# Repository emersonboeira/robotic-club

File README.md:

# robotic-club
Our robotics club repository

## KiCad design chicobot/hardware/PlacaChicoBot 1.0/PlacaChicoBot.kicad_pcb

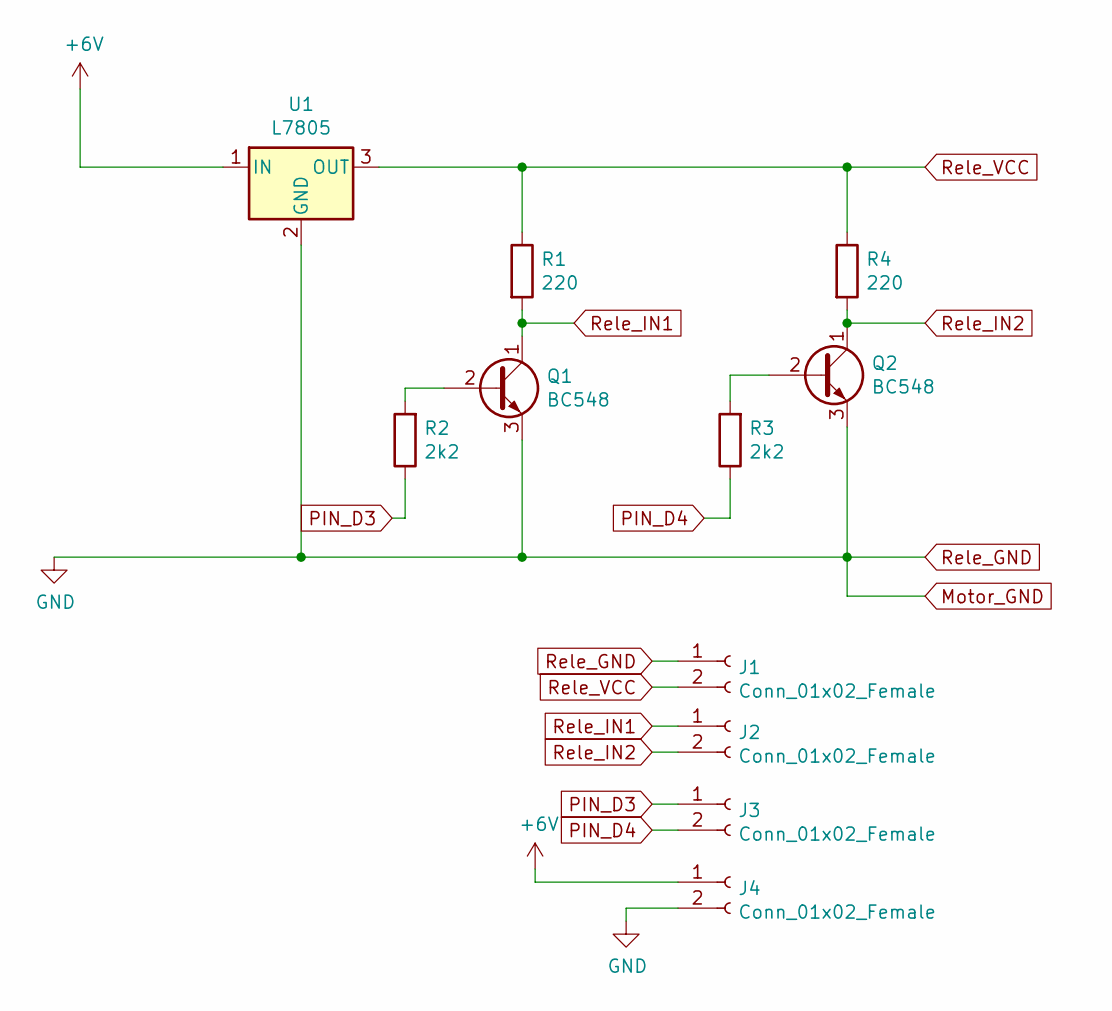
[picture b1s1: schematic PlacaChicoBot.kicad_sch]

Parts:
J1, J2, J3, J4: Conn_01x02_Female; TerminalBlock_Phoenix_MPT-0,5-2-2.54_1x02_P2.54mm_Horizontal
Q1, Q2: BC548; TO-92_Inline
R1, R4: 220; R_Axial_DIN0309_L9.0mm_D3.2mm_P12.70mm_Horizontal
R2, R3: 2k2; R_Axial_DIN0309_L9.0mm_D3.2mm_P12.70mm_Horizontal
U1: L7805; TO-220-3_Vertical

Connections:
+6V: J4.1, U1.1 (IN)
Motor_GND: J1.1, J4.2, Q1.3 (E), Q2.3 (E), U1.2 (GND)
unnamed: Q1.2 (B), R2.2
unnamed: Q2.2 (B), R3.2
PIN_D3: J3.1, R2.1
PIN_D4: J3.2, R3.1
Rele_IN1: J2.1, Q1.1 (C), R1.2
Rele_IN2: J2.2, Q2.1 (C), R4.2
Rele_VCC: J1.2, R1.1, R4.1, U1.3 (OUT)

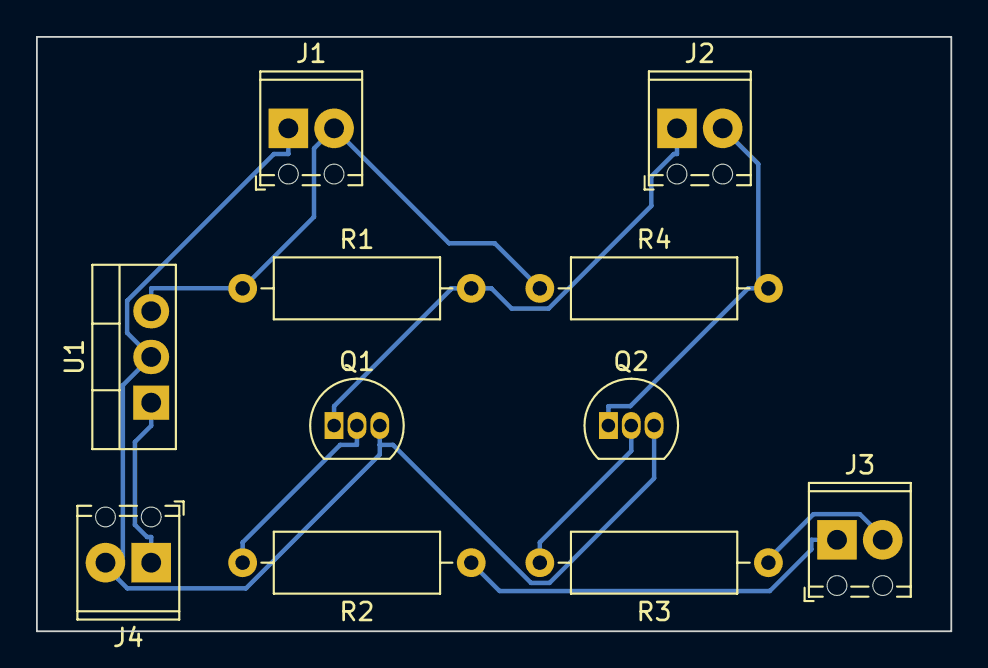
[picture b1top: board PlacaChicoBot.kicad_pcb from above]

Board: 2 copper layers, 50.8 x 33.0 mm, 11 parts (0 on the bottom side), 9 nets.

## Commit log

2022-07-25 Add chicobot v1 and v2 projects
